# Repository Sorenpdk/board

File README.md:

# Custom STM32F4 Board
## I want to make my own custom board. The idea is to work with various peripherals and a special interest in trying out the CMSIS DSP library.
### TODO
 - [x] Find suitable serial flash.
 - [ ] Find MEMS sensors
 	- [ ] Gyro and accelerometer
 	- [ ] Microphone
 	- [ ] Pressure sensor
 - [ ] ........

### Some goals
- [ ] CMSIS FFT on microphone and accelerometer.
- [ ] FIR and IIR filter implementation.
- [ ] Standard timer stuff for RGB led.
- [ ] USB power + 12VDC as main supply
- [ ] SWD programming.
- [ ] Custom bootloader.
- [ ] DMA and ADC
- [ ] ........

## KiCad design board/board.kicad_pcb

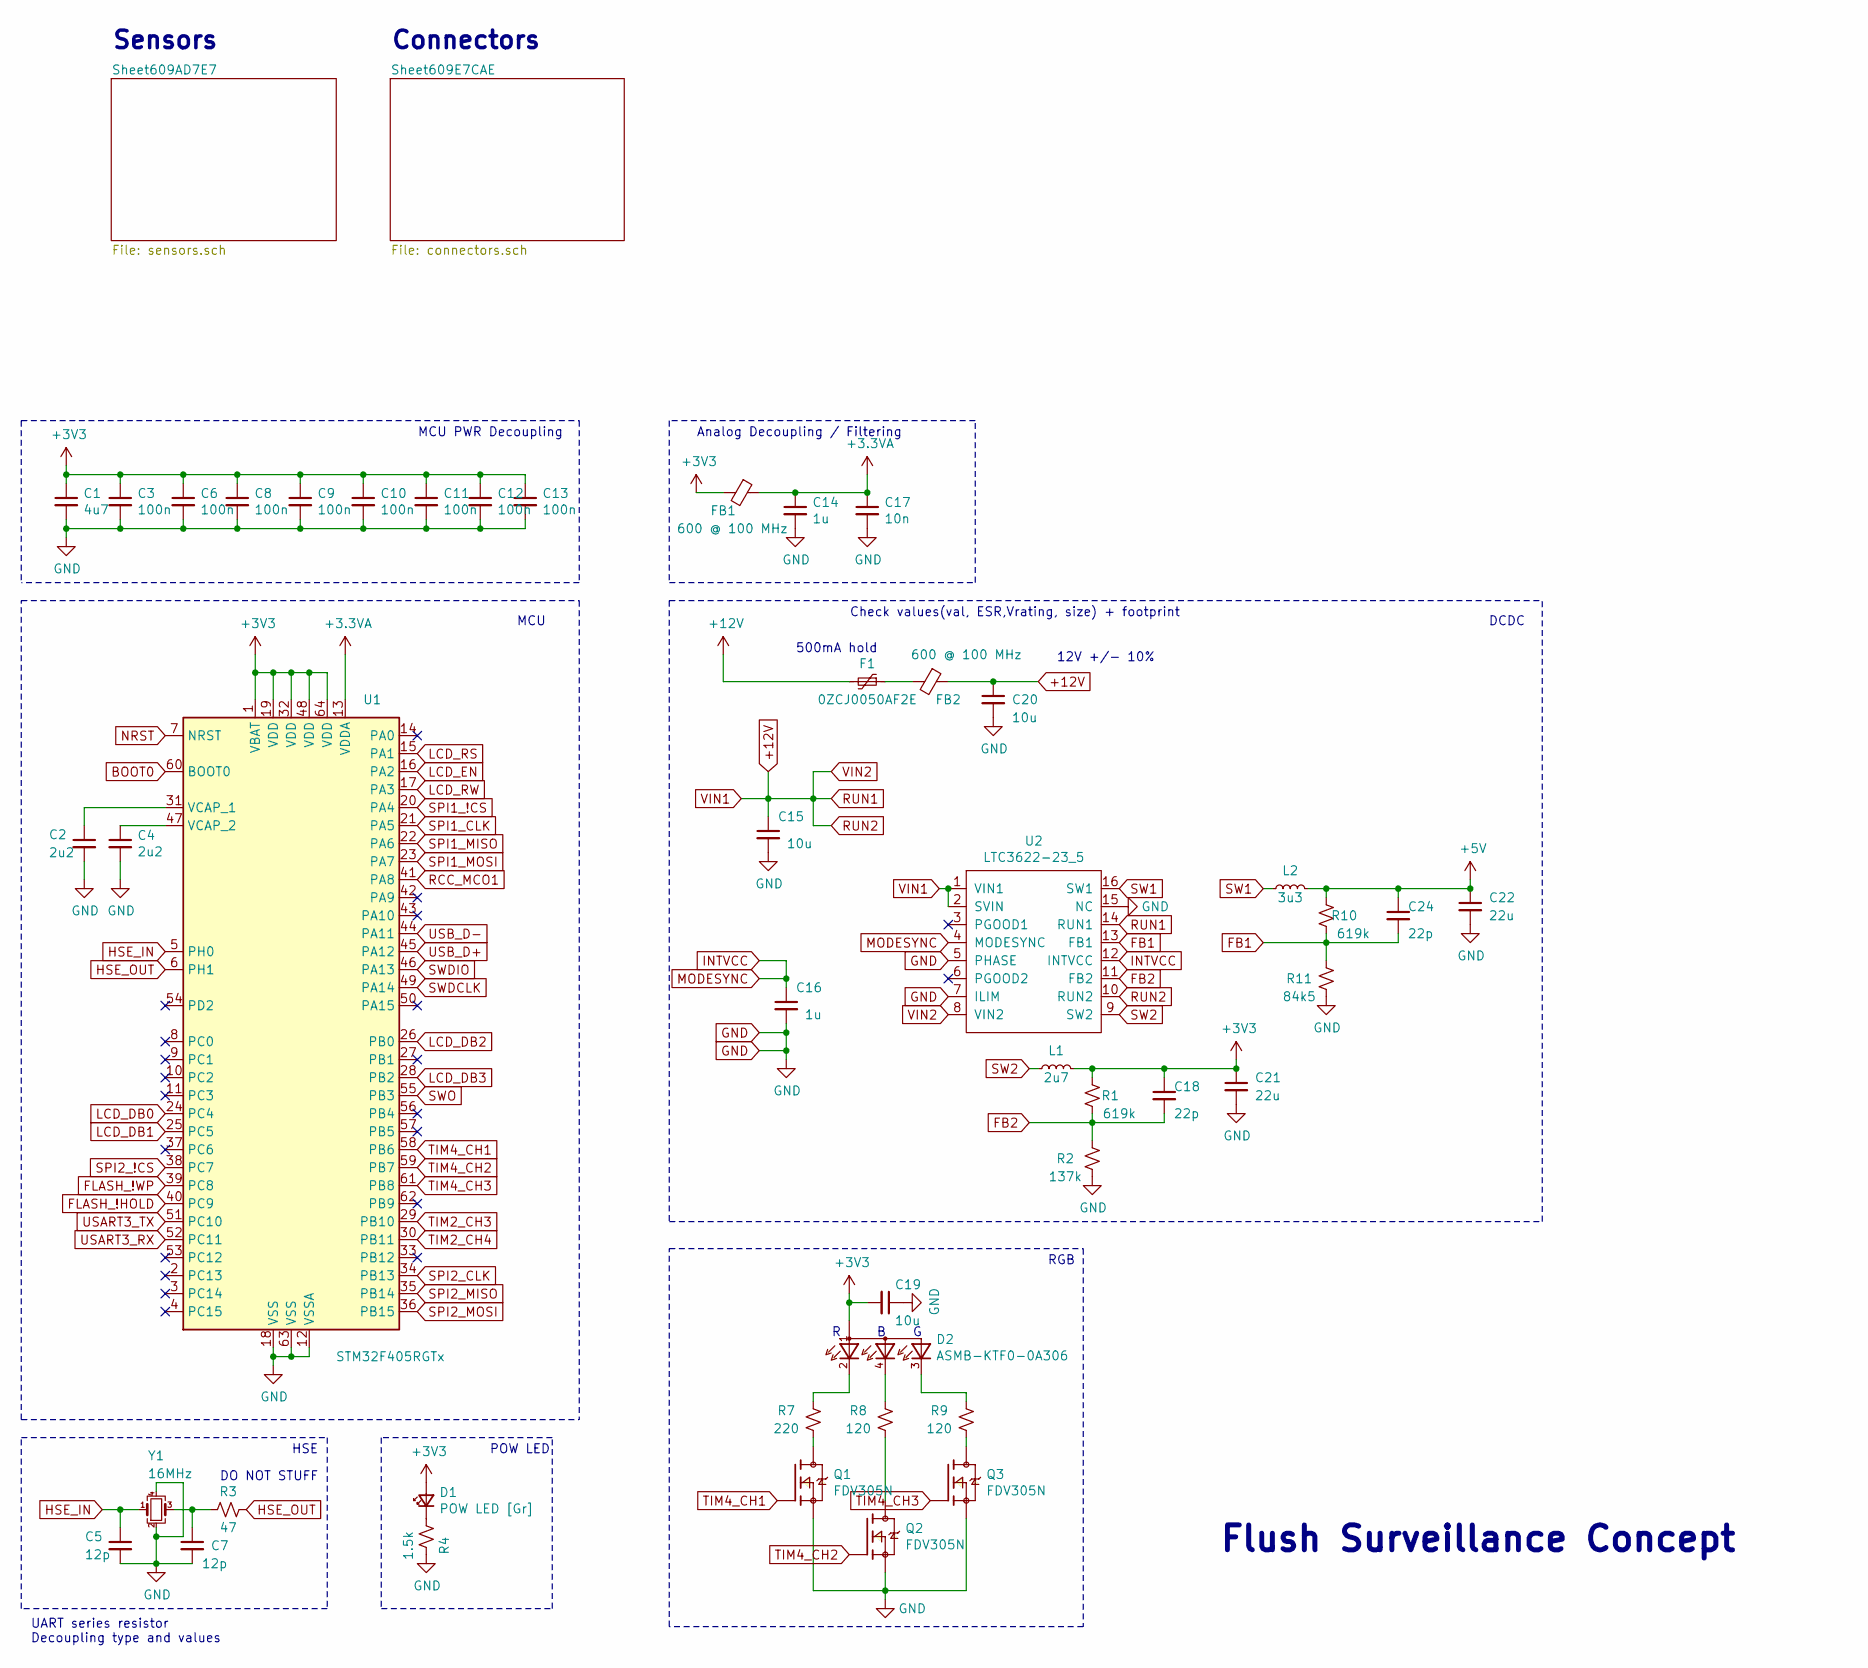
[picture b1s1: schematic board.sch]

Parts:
C1: 4u7; C_0603_1608Metric
C2, C4: 2u2; C_0603_1608Metric
C3, C6, C8, C9, C10, C11, C12, C13: 100n; C_0402_1005Metric
C5, C7: 12p; C_0402_1005Metric
C14, C16: 1u; C_0402_1005Metric
C15, C19, C20: 10u; C_0603_1608Metric
C17: 10n; C_0402_1005Metric
C18, C24: 22p; C_0402_1005Metric
C21, C22: 22u; C_0402_1005Metric
D1: POW LED [Gr]; LED_0603_1608Metric
D2: ASMB-KTF0-0A306; LED_ASMB-KTF0-0A306; PART_REV 15sep2017
F1: 0ZCJ0050AF2E; Fuse_1206_3216Metric
FB1, FB2: 600 @ 100 MHz; L_0603_1608Metric
L1: 2u7; L_0603_1608Metric
L2: 3u3; L_0603_1608Metric; LCSC Part # C370336
Q1, Q2, Q3: FDV305N; SOT95P240X111-3N; PARTREV 30 Jan 2018
R1, R10: 619k; R_0402_1005Metric
R2: 137k; R_0402_1005Metric
R3: 47; R_0402_1005Metric; LCSC Part # C478874
R4: 1.5k; R_0603_1608Metric
R7: 220; R_0603_1608Metric
R8, R9: 120; R_0603_1608Metric
R11: 84k5; R_0402_1005Metric
U1: STM32F405RGTx; LQFP-64_10x10mm_P0.5mm
U2: LTC3622-23_5; MSOP-16-1EP_3x4mm_P0.5mm_EP1.65x2.85mm_ThermalVias
Y1: 16MHz; Crystal_SMD_3225-4Pin_3.2x2.5mm; LCSC Part # C13738

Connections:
+3.3VA: C14.1, C17.1, FB1.1, U1.13 (VDDA)
+5V: C22.1, C24.1, L2.2, R10.2; also elsewhere on the board
+12V: C15.1, C20.1, F1.2, FB2.1, U2.1 (VIN1), U2.2 (SVIN), U2.8 (VIN2), U2.10 (RUN2), U2.14 (RUN1); also elsewhere on the board
BOOT0: U1.60 (BOOT0); also elsewhere on the board
FB1: C24.2, R10.1, R11.2, U2.13 (FB1)
FB2: C18.2, R1.1, R2.2, U2.11 (FB2)
FLASH_!HOLD: U1.40 (PC9); also elsewhere on the board
FLASH_!WP: U1.39 (PC8); also elsewhere on the board
GND: C1.2, C2.2, C3.2, C4.2, C5.2, C6.2, C7.2, C8.2, C9.2, C10.2, C11.2, C12.2, C13.2, C14.2, C15.2, C16.2, C17.2, C19.1, C20.2, C21.2, C22.2, Q1.2, Q2.2, Q3.2, R2.1, R4.1, R11.1, U1.12 (VSSA), U1.18 (VSS), U1.63 (VSS), U2.5 (PHASE), U2.7 (ILIM), U2.15 (NC), Y1.2, Y1.4; also elsewhere on the board
HSE_IN: C5.1, U1.5 (PH0), Y1.1
HSE_OUT: R3.1, U1.6 (PH1)
INTVCC: C16.1, U2.4 (MODESYNC), U2.12 (INTVCC)
LCD_DB0: U1.24 (PC4); also elsewhere on the board
LCD_DB1: U1.25 (PC5); also elsewhere on the board
LCD_DB2: U1.26 (PB0); also elsewhere on the board
LCD_DB3: U1.28 (PB2); also elsewhere on the board
LCD_EN: U1.16 (PA2); also elsewhere on the board
LCD_RS: U1.15 (PA1); also elsewhere on the board
LCD_RW: U1.17 (PA3); also elsewhere on the board
NRST: U1.7 (NRST); also elsewhere on the board
unnamed: C2.1, U1.31 (VCAP_1)
unnamed: C4.1, U1.47 (VCAP_2)
unnamed: C7.1, R3.2, Y1.3
unnamed: D1.1 (K), R4.2
unnamed: D2.2, R7.2
unnamed: D2.3, R9.2
unnamed: D2.4, R8.2
unnamed: F1.1, FB2.2
unnamed: Q1.3, R7.1
unnamed: Q2.3, R8.1
unnamed: Q3.3, R9.1
RCC_MCO1: U1.41 (PA8); also elsewhere on the board
SPI1_!CS: U1.20 (PA4); also elsewhere on the board
SPI1_CLK: U1.21 (PA5); also elsewhere on the board
SPI1_MISO: U1.22 (PA6); also elsewhere on the board
SPI1_MOSI: U1.23 (PA7); also elsewhere on the board
SPI2_!CS: U1.38 (PC7); also elsewhere on the board
SPI2_CLK: U1.34 (PB13); also elsewhere on the board
SPI2_MISO: U1.35 (PB14); also elsewhere on the board
SPI2_MOSI: U1.36 (PB15); also elsewhere on the board
SW1: L2.1, U2.16 (SW1)
SW2: L1.1, U2.9 (SW2)
SWDCLK: U1.49 (PA14); also elsewhere on the board
SWDIO: U1.46 (PA13); also elsewhere on the board
SWO: U1.55 (PB3); also elsewhere on the board
TIM2_CH3: U1.29 (PB10); also elsewhere on the board
TIM2_CH4: U1.30 (PB11)
TIM4_CH1: Q1.1, U1.58 (PB6)
TIM4_CH2: Q2.1, U1.59 (PB7)
TIM4_CH3: Q3.1, U1.61 (PB8)
USART3_RX: U1.52 (PC11); also elsewhere on the board
USART3_TX: U1.51 (PC10); also elsewhere on the board
USB_D+: U1.45 (PA12); also elsewhere on the board
USB_D-: U1.44 (PA11); also elsewhere on the board

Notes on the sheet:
Flush Surveillance Concept
MCU
HSE
UART series resistor Decoupling type and values
MCU PWR Decoupling
RGB
Check values(val, ESR,Vrating, size) + footprint
12V +/- 10%
DCDC
Analog Decoupling / Filtering
Connectors
Sensors
500mA hold
POW LED
DO NOT STUFF

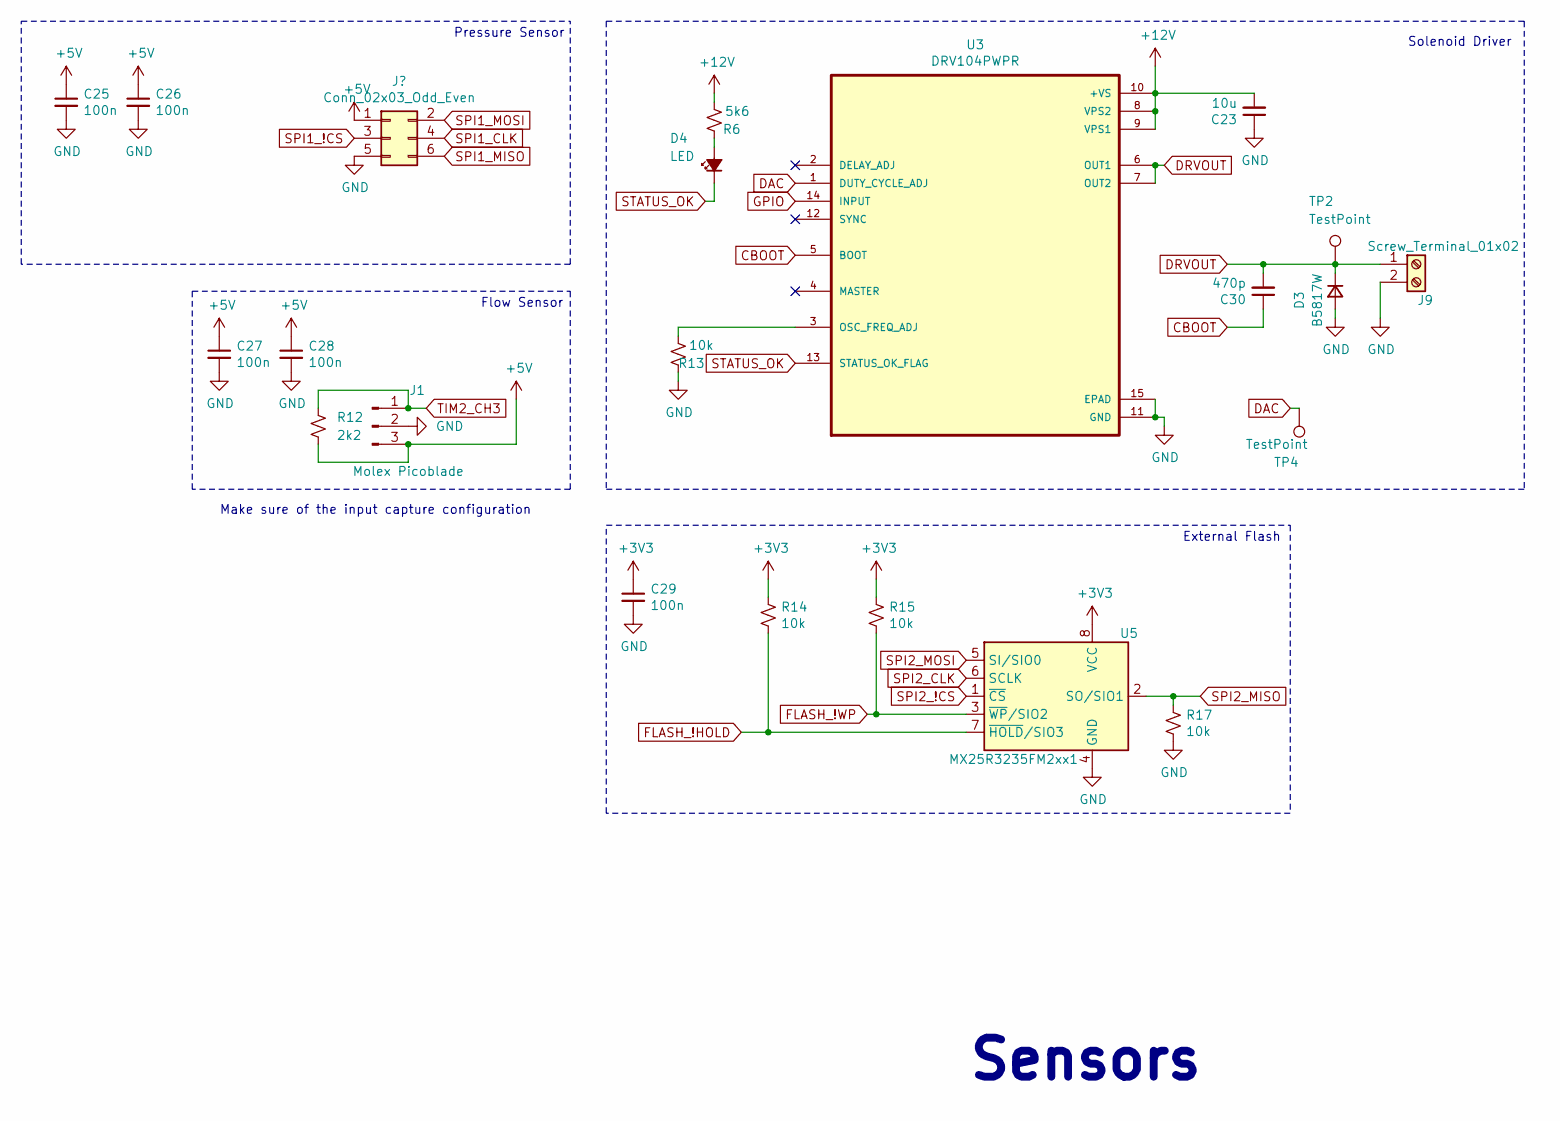
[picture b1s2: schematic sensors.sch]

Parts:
C23: 10u; C_0402_1005Metric
C25, C26, C27, C28, C29: 100n; C_0402_1005Metric
C30: 470p; C_0402_1005Metric
D3: B5817W; D_0805_2012Metric
D4: LED; LED_0603_1608Metric
J1: Molex Picoblade; JST_XH_B3B-XH-A_1x03_P2.50mm_Vertical
J9: Screw_Terminal_01x02; TerminalBlock_Phoenix_PT-1,5-2-5.0-H_1x02_P5.00mm_Horizontal
R6: 5k6; R_0603_1608Metric
R12: 2k2; R_0603_1608Metric
R13, R14, R15, R17: 10k; R_0603_1608Metric
TP2, TP4: TestPoint; TestPoint_Pad_D1.0mm
U3: DRV104PWPR; IC_TPS27S100BPWPR
U5: MX25R3235FM2xx1; SOP-8_5.28x5.23mm_P1.27mm

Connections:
+5V: C25.1, C26.1, C27.1, C28.1, J1.3, R12.2; also elsewhere on the board
+12V: C23.2, R6.2, U3.8 (VPS2), U3.9 (VPS1), U3.10 (+VS); also elsewhere on the board
CBOOT: C30.1, U3.5 (BOOT)
DAC: TP4.1, U3.1 (DUTY_CYCLE_ADJ)
DRVOUT: C30.2, D3.1 (K), J9.1, TP2.1, U3.6 (OUT1), U3.7 (OUT2)
FLASH_!HOLD: R14.2, U5.7 (~HOLD~/SIO3); also elsewhere on the board
FLASH_!WP: R15.2, U5.3 (~WP~/SIO2); also elsewhere on the board
GND: C23.1, C25.2, C26.2, C27.2, C28.2, C29.2, D3.2 (A), J1.2, J9.2, R13.1, R17.2, U3.11 (GND), U3.15 (EPAD), U5.4 (GND); also elsewhere on the board
GPIO: U3.14 (INPUT)
unnamed: D4.2 (A), R6.1
unnamed: R13.2, U3.3 (OSC_FREQ_ADJ)
SPI2_!CS: U5.1 (~CS); also elsewhere on the board
SPI2_CLK: U5.6 (SCLK); also elsewhere on the board
SPI2_MISO: R17.1, U5.2 (SO/SIO1); also elsewhere on the board
SPI2_MOSI: U5.5 (SI/SIO0); also elsewhere on the board
STATUS_OK: D4.1 (K), U3.13 (STATUS_OK_FLAG)
TIM2_CH3: J1.1, R12.1; also elsewhere on the board

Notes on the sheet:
Solenoid Driver
Pressure Sensor
Flow Sensor
External Flash
Make sure of the input capture configuration
Sensors

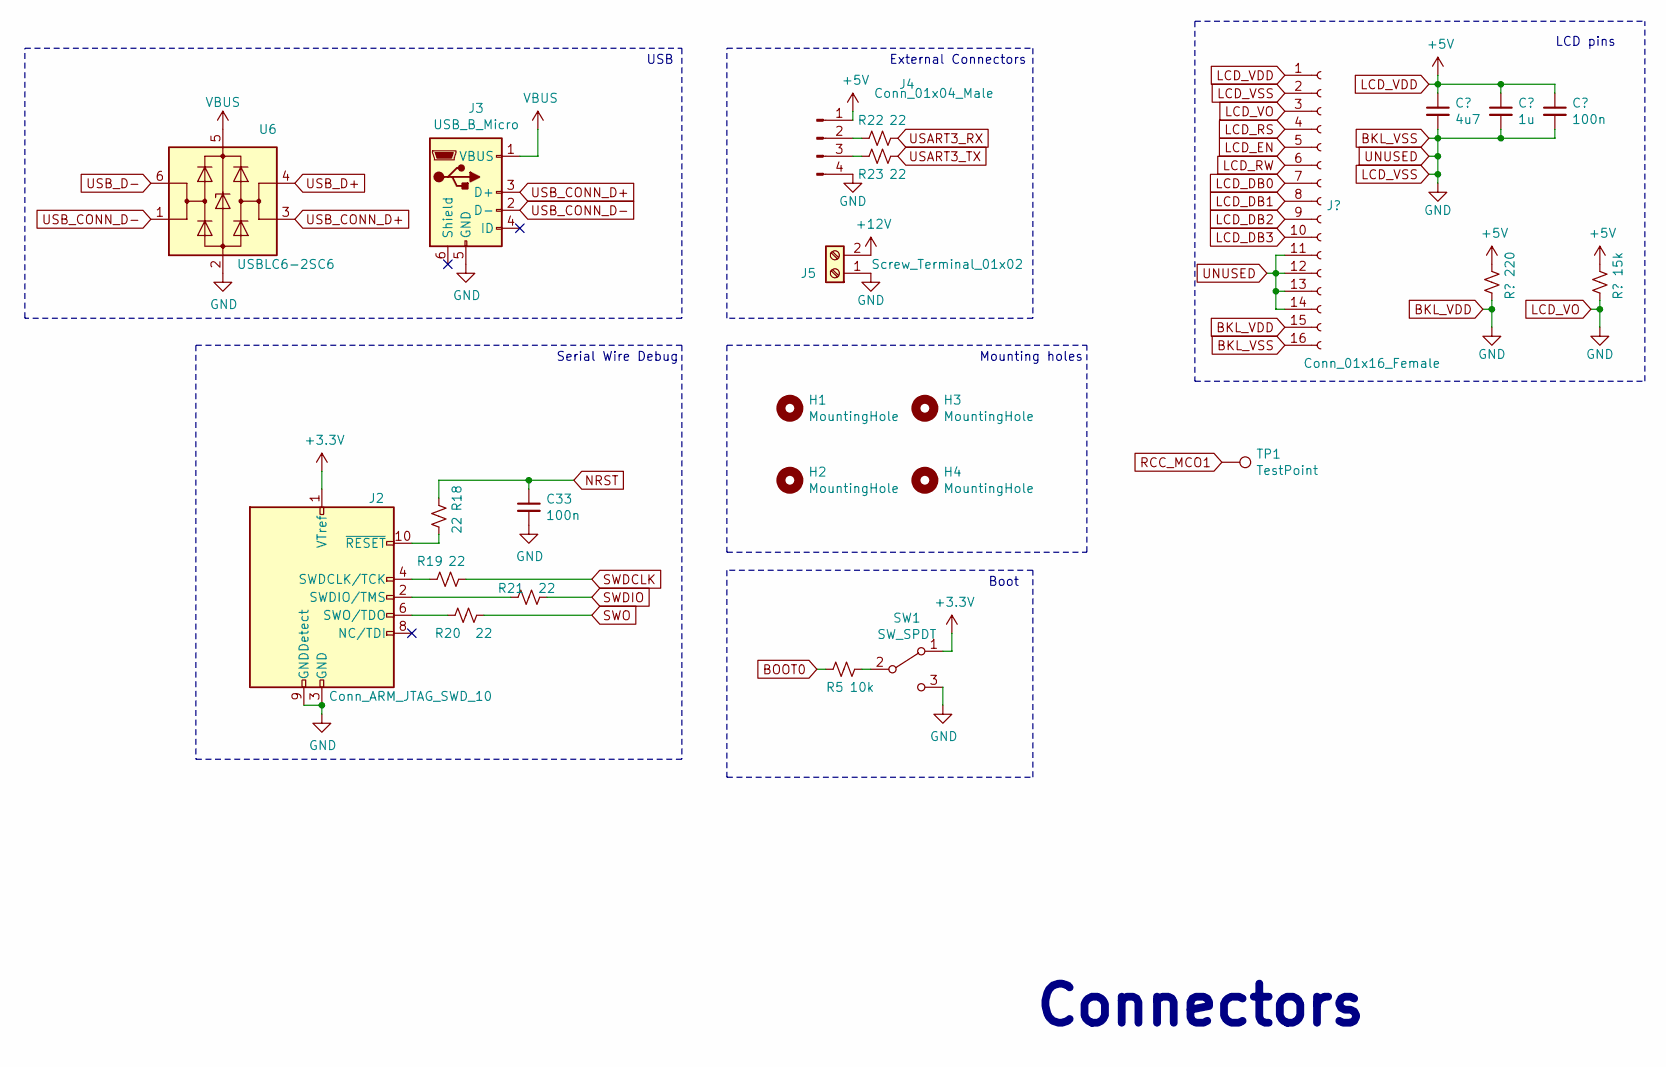
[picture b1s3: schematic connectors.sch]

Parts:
C33: 100n; C_0402_1005Metric
H1, H2, H3, H4: MountingHole; MountingHole_3.5mm_Pad_Via
J2: Conn_ARM_JTAG_SWD_10; PinHeader_2x05_P1.27mm_Vertical_SMD
J3: USB_B_Micro; USB_Micro-B_Molex_47346-0001
J4: Conn_01x04_Male; PinHeader_1x04_P2.54mm_Vertical
J5: Screw_Terminal_01x02; TerminalBlock_Phoenix_PT-1,5-2-5.0-H_1x02_P5.00mm_Horizontal
R5: 10k; R_0603_1608Metric
R18, R19, R20, R21, R22, R23: 22; R_0603_1608Metric
SW1: SW_SPDT; SW_SPDT_PCM12
TP1: TestPoint; TestPoint_Pad_D1.0mm
U6: USBLC6-2SC6; SOT-23-6

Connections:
+5V: J4.1; also elsewhere on the board
+12V: J5.2; also elsewhere on the board
BOOT0: R5.2; also elsewhere on the board
GND: C33.2, J2.3 (GND), J2.5 (GND), J2.9 (GNDDetect), J3.5 (GND), J4.4, J5.1, SW1.3 (C), U6.2 (GND); also elsewhere on the board
NRST: C33.1, R18.2; also elsewhere on the board
unnamed: J2.2 (SWDIO/TMS), R21.2
unnamed: J2.4 (SWDCLK/TCK), R19.2
unnamed: J2.6 (SWO/TDO), R20.2
unnamed: J2.10 (~RESET~), R18.1
unnamed: J4.2, R22.2
unnamed: J4.3, R23.2
unnamed: R5.1, SW1.2 (B)
RCC_MCO1: TP1.1; also elsewhere on the board
SWDCLK: R19.1; also elsewhere on the board
SWDIO: R21.1; also elsewhere on the board
SWO: R20.1; also elsewhere on the board
USART3_RX: R22.1; also elsewhere on the board
USART3_TX: R23.1; also elsewhere on the board
USB_CONN_D+: J3.3 (D+), U6.3 (I/O2)
USB_CONN_D-: J3.2 (D-), U6.1 (I/O1)
USB_D+: U6.4 (I/O2); also elsewhere on the board
USB_D-: U6.6 (I/O1); also elsewhere on the board
VBUS: J3.1 (VBUS), U6.5 (VBUS)

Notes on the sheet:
USB
Mounting holes
Serial Wire Debug
External Connectors
Connectors
LCD pins
Boot

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
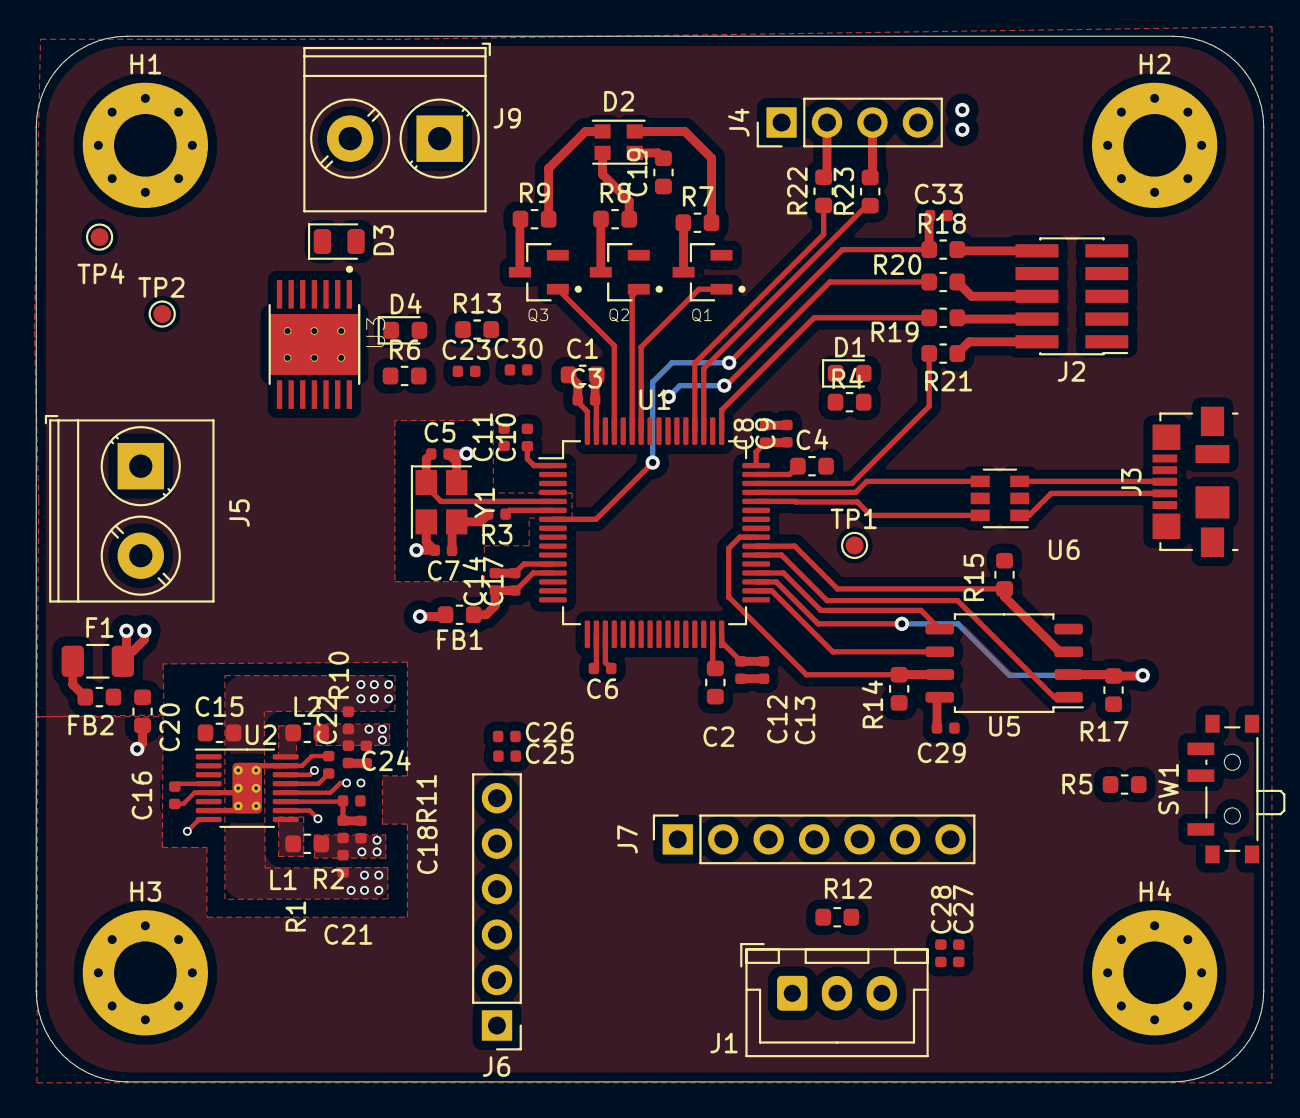
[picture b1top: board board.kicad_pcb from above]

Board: 4 copper layers, 68.6 x 58.4 mm, 87 parts (0 on the bottom side), 70 nets.

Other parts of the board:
J6: Conn_01x06_Male; PinHeader_1x06_P2.54mm_Vertical
J7: Conn_01x07_Female; PinSocket_1x07_P2.54mm_Vertical

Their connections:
+5V: J6.6; also elsewhere on the board
GND: J6.1; also elsewhere on the board
LCD_DB0: J7.4; also elsewhere on the board
LCD_DB1: J7.5; also elsewhere on the board
LCD_DB2: J7.6; also elsewhere on the board
LCD_DB3: J7.7; also elsewhere on the board
LCD_EN: J7.2; also elsewhere on the board
LCD_RS: J7.1; also elsewhere on the board
LCD_RW: J7.3; also elsewhere on the board
SPI1_!CS: J6.5; also elsewhere on the board
SPI1_CLK: J6.3; also elsewhere on the board
SPI1_MISO: J6.2; also elsewhere on the board
SPI1_MOSI: J6.4; also elsewhere on the board

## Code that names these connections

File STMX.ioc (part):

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Mcu.Name=STM32F405RGTx
Mcu.Package=LQFP64
Mcu.UserName=STM32F405RGTx
PA1.GPIOParameters=GPIO_Label
PA1.GPIO_Label=LCD_RW
PA1.Signal=GPIO_Output
PA11.Mode=Device_Only
PA11.Signal=USB_OTG_FS_DM
PA12.Mode=Device_Only
PA12.Signal=USB_OTG_FS_DP
PA13.Mode=Trace_Asynchronous_SW
PA13.Signal=SYS_JTMS-SWDIO
PA14.Mode=Trace_Asynchronous_SW
PA14.Signal=SYS_JTCK-SWCLK
PA15.GPIOParameters=GPIO_Label
PA15.GPIO_Label=SPI3_\!CS
PA15.Signal=GPIO_Output
PA2.GPIOParameters=GPIO_Label
PA2.GPIO_Label=LCD_RS
PA2.Signal=GPIO_Output
PA4.Signal=COMP_DAC1_group
PA6.Signal=S_TIM3_CH1
PA7.GPIOParameters=GPIO_Label
PA7.GPIO_Label=LCD_DB3
PA7.Signal=GPIO_Output
PA8.Mode=Clock-out-1
PA8.Signal=RCC_MCO_1
PB0.GPIOParameters=GPIO_Label
PB0.GPIO_Label=LCD_DB0
PB0.Signal=GPIO_Output
PB1.GPIOParameters=GPIO_Label
PB1.GPIO_Label=LCD_EN
PB1.Signal=GPIO_Output
PB10.Mode=Asynchronous
PB10.Signal=USART3_TX
PB11.Mode=Asynchronous
PB11.Signal=USART3_RX
PB12.GPIOParameters=GPIO_Label
PB12.GPIO_Label=SPI2_\!CS
PB12.Signal=GPIO_Output
PB13.Mode=Full_Duplex_Master
PB13.Signal=SPI2_SCK
PB14.Mode=Full_Duplex_Master
PB14.Signal=SPI2_MISO
PB15.Mode=Full_Duplex_Master
PB15.Signal=SPI2_MOSI
PB3.Mode=Trace_Asynchronous_SW
PB3.Signal=SYS_JTDO-SWO
PB6.Signal=S_TIM4_CH1
PB7.Signal=S_TIM4_CH2
PB8.Signal=S_TIM4_CH3
PC0.Signal=ADCx_IN10
PC1.Signal=ADCx_IN11
PC10.Mode=Full_Duplex_Master
PC10.Signal=SPI3_SCK
PC11.Mode=Full_Duplex_Master
PC11.Signal=SPI3_MISO
PC12.Mode=Full_Duplex_Master
PC12.Signal=SPI3_MOSI
PC3.GPIOParameters=GPIO_Label
PC3.GPIO_Label=DRV_EN
PC3.Signal=GPIO_Output
PC4.GPIOParameters=GPIO_Label
PC4.GPIO_Label=LCD_DB2
PC4.Signal=GPIO_Output
PC5.GPIOParameters=GPIO_Label
PC5.GPIO_Label=LCD_DB1
PC5.Signal=GPIO_Output
PC6.GPIOParameters=GPIO_Label
PC6.GPIO_Label=FLASH_\!WP
PC6.Signal=GPIO_Output
PC7.GPIOParameters=GPIO_Label
PC7.GPIO_Label=FLASH_\!HOLDm
PC7.Signal=GPIO_Output
PH0-OSC_IN.Mode=HSE-External-Oscillator
PH0-OSC_IN.Signal=RCC_OSC_IN
PH1-OSC_OUT.Mode=HSE-External-Oscillator
PH1-OSC_OUT.Signal=RCC_OSC_OUT
RCC.HSE_VALUE=16000000
RCC.SYSCLKFreq_VALUE=168000000
RCC.SYSCLKSource=RCC_SYSCLKSOURCE_PLLCLK
board=custom

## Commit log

2021-05-02 Pushing for Kicad reinstall
2021-05-03 Small update on power section
2021-05-03 quick push
2021-05-04 Updated board.pdf
2021-05-04 Updated board schematic
2021-05-11 Updated board
2021-05-19 Rework on power supply and added pressure sensor
2021-05-26 Generic update
2021-05-31 Update on pinout
2021-06-01 Updated schematic
2021-06-01 Updated footprints
2021-06-01 Updated layout
2021-06-23 Push
2021-06-23 Take 2
